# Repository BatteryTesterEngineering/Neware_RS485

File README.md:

# Neware BTS4000 RS-485 Protocol
This work is the reverse engineering of the Neware BTS4000 series battery cyclers RS-485 communication protocol.

## Division of Responsibilities
The Middle Machine is responsible for control and intepretation of the vast majority of the battery testing process, while the battery cyclers exclusively respond to commands from the middle machine.

For example, the termination conditions for test steps are evaluated and handled by the middle machine. The cyclers report current and voltage values as ADC readings, which the middle machine then converts to physical values. The testers themselves do run the active feedback control to maintain specified physical conditions: current, power, voltage, etc.

| Middle Machine   | Tester         | 
| --------- | ------------- | 
| Evaluates step termination conditions | Active feedback control to maintain step conditions (IE constant current, constant power, etc.) |
| Converts ADC values to physical values |  Sets channel LED status based on channel activity       | 
| Sets the data aquisition frequency    | Continuously Samples the ADCs  |

## RS-485 Bus
The Neware BTS4000 battery cycler system uses a full-duplex, 3 Mbps RS-485 physical bus to connect the middle machine to all of the test units.

RS-485 layout from [Neware's official guide](https://newarebattery.com/how-to-start-to-use-neware-bst4000-series/)

### Bus UART Settings

| Setting   | Value         | 
| --------- | ------------- | 
| Baud Rate | 3,000,000 bps | 
| Byte Size | 8 bits        | 
| Parity    | None          | 
| Stop Bits | 1             | 

### Full-Duplex
The RS-485 implementation by Neware is ***full-duplex***. Note that this is relatively unusual for RS-485 implementations. That means that the controller (middle machine) transmits messages on one channel (twisted copper pair), and the receivers (testers) transmit on another channel. 

> Side note: This could have been implemented as a half-duplex bus. This full-duplex communication is not technically needed, as the middle machine must send a request before any tester responds and the testers only respond after the middle machine requests. However, if the two channels are bridged, the communications fail between the middle machine and the testers. So, I guess, full-duplex it is.

### Pinout
The Neware BTS4000 middle machine and testers use RJ45 jacks and standard ethernet cables for RS-485 communications. Each machine has two ports which are wired in electrical parallel to allow for easy daisy chaining. There is no difference between the two ports.

The pinout is as follows:

| Middle Machine Function  | Tester Function | Ethernet Wire Color (T568B) | RJ45 Pin |
| ------ | ------ | ------------ | - |
| R- (B) | T- (Z) | Green        | 6 |
| R+ (A) | T+ (Y) | Green/White  | 3 |
| T- (Z) | R- (B) | Orange       | 2 |
| T+ (Y) | R+ (A) | Orange/White | 1 |
| GND    | GND    | Brown        | 8 |
| GND    | GND    | Brown/White  | 7 |

> RJ45 pins 4 and 5 (Ethernet T568B colors Blue and Blue/White) are unused.

## Neware Communication Protocol
The protocol appears to be a custom implementation on top of RS-485 and does not follow common standards such as Modbus RTU, Profibus, DMX512, BACnet MS/TP, etc.

### Overview
The middle machine begins all communications. Every response from the testers is a direct response to a request from the middle machine. The testers have a watchdog timeout such that they will turn off all charge or discharge activity on all channels if they do not hear a message from the middle machine every few seconds.

Every message is 36 bytes long and consists of one byte of machine addressing, one byte of channel addressing, one byte of message type ID, a one byte CRC, and 32 bytes of payload.

| byte 0 | byte 1 | byte 2 | byte 3 | bytes 4 - 35 |
| ------ | ------ | ------ | ------ | ------------ |
| Machine ID | Channel ID | Message Type ID | CRC | Message Type Dependent Payload

> Note: There is no time information provided by the testers. All timestamps are added upon message reception by the middle machine.

### Machine Addressing
Machine ID is 0 indexed, while it is presented to the user as 1 indexed. IE Machine ID 0 corresponds to the tester with ID 1.

### Channel Addressing
Channel ID is 0 indexed, while it is presented to the user as 1 indexed. IE Channel ID 7 corresponds to the tester Channel 8.

### Message Type ID
The message type ID byte defines what the message type is. Specifically, bit 0 is flag for request ('0' if the message is a request/comes from the middle machine) or response ('1' if the message is a response/comes from a tester), and the remaining seven bits define the message type.

| bit 0 | bits 1-7 |
| ----- | -------- |
| Request (0) / Response (1) Flag | Message Type |

Some known message type IDs are defined below:

| ID | Description |
| ----- | -------- |
| 0x00  | Tester Response (Ping) Request |
| 0x80  | Tester Presence (Ping) Acknowledge |
| 0x02  | Change Unit ID Request |
| 0x82  | Change Unit ID Acknowledge |
| 0x17  | Constant Voltage Charge Request |
| 0x97  | Constant Voltage Charge Acknowledge |
| 0x18  | Constant Voltage Discharge Request |
| 0x98  | Constant Voltage Discharge Acknowledge |
| 0x1A  | Constant Current Charge Request |
| 0x9A  | Constant Current Charge Acknowledge |
| 0x1B  | Constant Current Discharge Request |
| 0x9B  | Constant Current Discharge Acknowledge |
| 0x1C  | Constant Power Discharge Request |
| 0x9C  | Constant Power Discharge Acknowledge |
| 0x1F  | Voltage and Current Request |
| 0x9F  | Voltage and Current Acknowledge |
| 0x25  | End of Test Request |
| 0xA5  | End of Test Acknowledge |
| 0x31  | Constant Power Charge Request |
| 0xB1  | Constant Power Charge Acknowledge |

### CRC
The CRC byte is a crc8-maxim-dow calculated on a modified message. Since the CRC byte is in the middle of the message instead of at the end, the process of using it is a bit unusual. The CRC is calculated on the full 36 byte message, with a dummy 0x00 value subbed into byte 3. The calculated CRC is then swapped into byte 3 before the message is transmitted.

**Transmission CRC Calculation**:
1. Build the message as intended, leave a dummy '0x00' value in byte 3.
2. Calculate the CRC using a crc8-maxim-dow algorithm on the 36 byte message with the dummy byte.
3. Place the calculated CRC in byte 3.
4. Transmit the 36 byte message.

**Reception CRC Checking**:
1. Receive the 36 byte message.
2. Copy the CRC out of byte 3.
3. Replace byte 3 with '0x00'
4. Calculate the CRC using a crc8-maxim-dow algorithm on the 36 byte message with the dummy byte
5. Compare the calculated CRC with the stored CRC from the message, checking for equality

-- Or --

4. Append the copied CRC byte to the end of the message
5. Calculate the CRC using a crc8-maxim-dow algorithm on the now 37 byte array (message + appended CRC)
6. Check the calculated CRC for equality with '0x00'

### Payload
The payload is message type dependent. Some known payloads are described below.

**Message 0x17: Constant Voltage Charge Request**

| Name | Byte Position | Physical Value to Bus Value Mapping |
| ----- | -------- | ----- |
| Voltage  | Bytes 4-7 | Physical Value = Bus Value / 3225.6 |

**Message 0x97: Constant Voltage Charge Acknowledge**

There is no payload for a Constant Voltage Charge Acknowledge

**Message 0x1A: Constant Current Charge Request**

| Name | Byte Position | Physical Value to Bus Value Mapping |
| ----- | -------- | ----- |
| Current  | Bytes 4-7 | Physical Value = Bus Value / Current Range Divisor |
| Current Range  | Byte 8 | See Table in 0x9F: Voltage and Current Acknowledge |

**Message 0x9A: Constant Current Charge Acknowledge**

There is no payload for a Constant Current Charge Acknowledge

**Message 0x1B: Constant Current Discharge Request**

| Name | Byte Position | Physical Value to Bus Value Mapping |
| ----- | -------- | ----- |
| Current  | Bytes 4-7 | Physical Value = Bus Value / Current Range Divisor |
| Current Range  | Byte 8 | See Table in 0x9F: Voltage and Current Acknowledge |

**Message 0x9B: Constant Current Discharge Acknowledge**

There is no payload for a Constant Current Discharge Acknowledge

**Message 0x1C: Constant Power Discharge Request**

| Name | Byte Position | Physical Value to Bus Value Mapping |
| ----- | -------- | ----- |
| Power  | Bytes 4-7 | Physical Value = Bus Value / Power Range Divisor |
| Power Range  | Byte 12 | See Table |

Strangely, only power range of 0x02 has ever been seen in logs, when setting the power value from 0.5W to 60W

| Power Range | Name | Description | Power Range Divisor |
| ----- | -------- | ----- | -------- |
| 0x00  | Low Range | ? A | ? |
| 0x01  | Mid Range | ? A | ? |
| 0x02  | High Range | 0 - 60 W | 268.8 |

**Message 0x9C: Constant Power Discharge Acknowledge**

There is no payload for a Constant Power Discharge Acknowledge

**Message 0x1F: Voltage and Current Request**

There is no payload for a Voltage and Current Request

**Message 0x9F: Voltage and Current Acknowledge**

| Name | Byte Position | Physical Value to Bus Value Mapping |
| ----- | -------- | ----- |
| Voltage  | Bytes 4-7 | Physical Value = Bus Value / 3225.6 |
| Current  | Bytes 8-11 | Physical Value = Bus Value / Current Range Divisor |
| Current Range  | Byte 33 | See Table |
| Channel Status | Byte 35 | See Table |

| Current Range | Name | Description | Current Range Divisor |
| ----- | -------- | ----- | -------- |
| 0x00  | Low Range | 0 - 1 A | 16128 |
| 0x01  | Mid Range | 1 - 6 A | 2688 |
| 0x02  | High Range | 6 - 12 A | 1344 |

| Channel Status | Description |
| ----- | ----- |
| 0x00  | Channel Active |
| 0x01  | Channel Invalid/Error |
| 0x02  | Channel Rest |

**Message 0x25: End of Test Request**

There is no payload for an End of Test Request

**Message 0xA5: End of Test Acknowledge**

There is no payload for an End of Test Acknowledge

**Message 0x31: Constant Power Charge Request**

| Name | Byte Position | Physical Value to Bus Value Mapping |
| ----- | -------- | ----- |
| Power  | Bytes 4-7 | Physical Value = Bus Value / Power Range Divisor |
| Power Range  | Byte 12 | See Table |

Strangely, only power range of 0x02 has ever been seen in logs, when setting the power value from 0.5W to 60W

| Power Range | Name | Description | Power Range Divisor |
| ----- | -------- | ----- | -------- |
| 0x00  | Low Range | ? A | ? |
| 0x01  | Mid Range | ? A | ? |
| 0x02  | High Range | 0 - 60 W | 268.8 |

**Message 0xB1: Constant Power Charge Acknowledge**

There is no payload for a Constant Power Charge Acknowledge

***TODO! Add more***

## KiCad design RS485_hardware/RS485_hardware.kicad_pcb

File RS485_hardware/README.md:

# Neware BTS4000 RS485 USB Interface

This is the Kicad project and output files for a USB Adapter that allows any computer to listen and transmit on the Neware BTS4000 RS485 bus. The adapter is based on the FTDI FT232RN chip, which includes drivers for all major operating systems. The transciever is a MaxLinear SP3077E, which allows for full duplex 3MBaud communication.

## RS485 Bus Connectors
The bus connectors are intended to duplicate the RS485 bus connections on a Middle Machine or Battery Tester. There are 2 RJ45 Jacks which are wired in parallel, allowing the device to be used in the same daisy-chain fashion as a Neware device. 

## Switches
The adapter includes 2 slide switches.

### Switch 1
Toggles the adapter between "Middle Machine Mode" and "Tester Mode". Since the RS485 bus is a full duplex bus, it matters which line the adapter is receiving on, and which it is transmitting on. With the switch slid towards the RJ45 jacks, the adapter acts as a middle machine, receiving on the same line that battery testers are transmitting on, and transmitting on the line that battery testers are receiving on. With the switch slid towards the USB-C jack, the adapter acts as tester, receiving from the middle machine and transmitting to the middle machine.

| Switch Position | Adapter Mode | Adapter TX | Adapter RX | LED Color |
| ------ | ------ | ------ | ------ | ------ |
| Towards RJ45 | Middle Machine | Middle Machine TX | Middle Machine RX | Blue |
| Towards USB-C | Tester | Middle Machine RX | Middle Machine TX | Red |

### Switch 2
Toggles the RS485 Termination Resistors on or off. With the switch slid towards the RJ45 jacks, there are no termination resistors on the bus. With the switch slid towards the USB-C jack, the adapter terminates the TX and RX busses with a 120Ω resistor on each bus. Whether or not you need the termination resistors enabled dependes on the length of the bus and what other devices are on the bus. A typical RS485 bus has a temination resistor enabled on both physical ends of the bus.

## PC Connection
The connection to a computer is a USB-C connector configured to run at USB 2.0 speeds. The USB connector has 5.1kΩ resistors on the CC lines, which allow it to work with USB C<->C cables or USB A<->C cables.

# Manufacturing
The ```outputs/manufacturing_files``` subfolder contains gerber and OBD files needed for PCB manufacturing, as well as the BOM file. The BOM contains manufacturer and part number data for digikey and LCSC to make sourcing parts easy regardless of where the boards are manufactured.

## Hand Assembly
All passives are 0603 or larger, with the large-pad footprints chosen to allow for hand soldering. Similarly, the pitch of all components should be large enough for hand soldering.

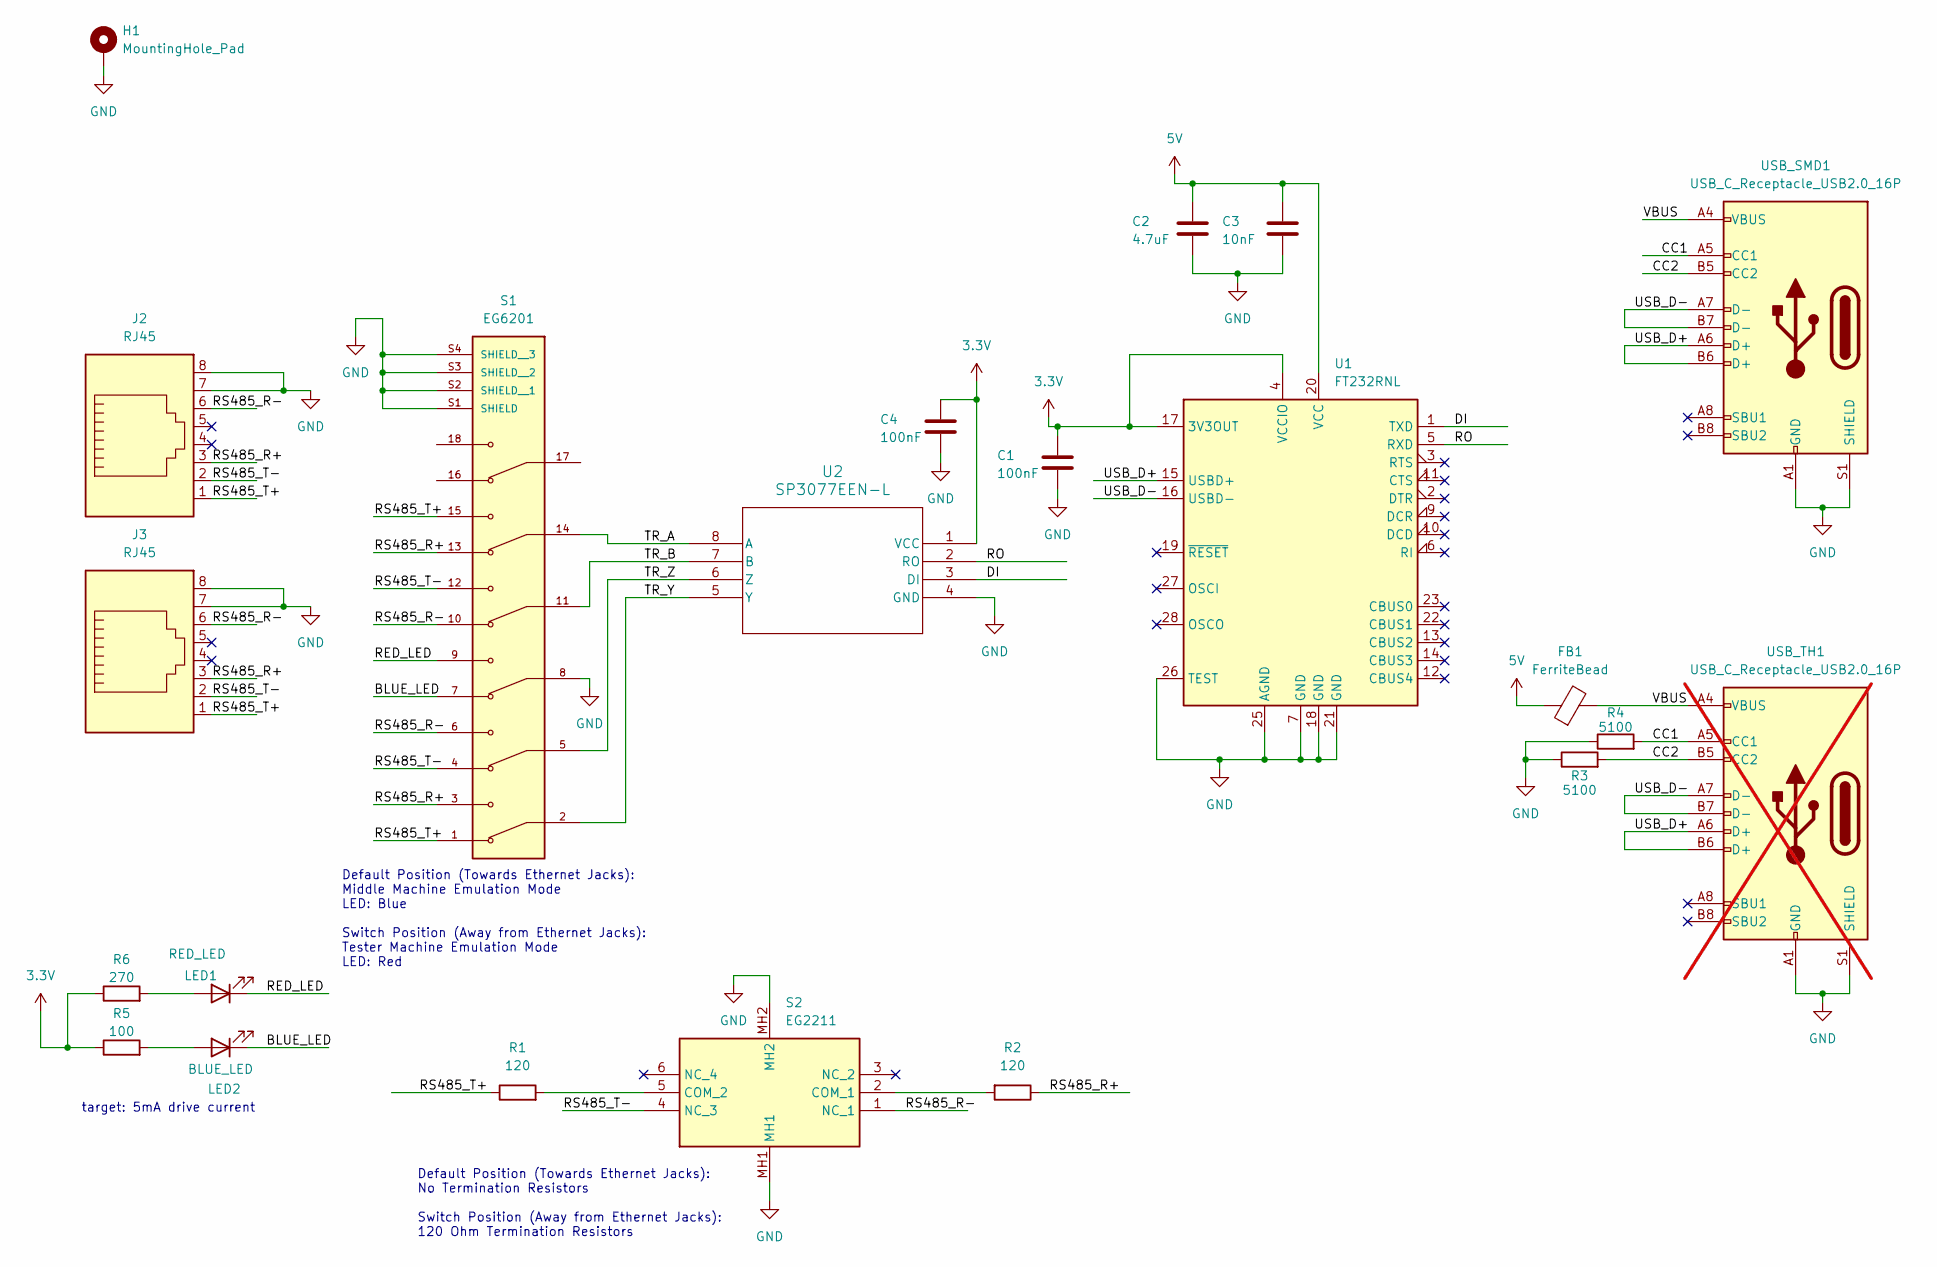
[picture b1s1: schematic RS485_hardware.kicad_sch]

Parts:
C1, C4: 100nF; C_0603_1608Metric_Pad1.08x0.95mm_HandSolder
C2: 4.7uF; C_0603_1608Metric_Pad1.08x0.95mm_HandSolder
C3: 10nF; C_0603_1608Metric_Pad1.08x0.95mm_HandSolder
FB1: FerriteBead; L_0805_2012Metric_Pad1.05x1.20mm_HandSolder
H1: MountingHole_Pad; MountingHole_3.2mm_M3_DIN965_Pad
J2, J3: RJ45; RJ45_Amphenol_54602-x08_Horizontal
LED1: RED_LED; LED_0603_1608Metric_Pad1.05x0.95mm_HandSolder
LED2: BLUE_LED; LED_0603_1608Metric_Pad1.05x0.95mm_HandSolder
R1, R2: 120; R_0603_1608Metric_Pad0.98x0.95mm_HandSolder
R3, R4: 5100; R_0603_1608Metric_Pad0.98x0.95mm_HandSolder
R5: 100; R_0603_1608Metric_Pad0.98x0.95mm_HandSolder
R6: 270; R_0603_1608Metric_Pad0.98x0.95mm_HandSolder
S1: EG6201; SW_EG6201; PARTREV B
S2: EG2211; Mouser Part Number 612-EG2211
U1: FT232RNL; SSOP-28_5.3x10.2mm_P0.65mm
U2: SP3077EEN-L; SOIC8_3P99X4P98
USB_SMD1: USB_C_Receptacle_USB2.0_16P; USB_C_Receptacle_GCT_USB4105-xx-A_16P_TopMnt_Horizontal
USB_TH1: USB_C_Receptacle_USB2.0_16P; USB_C_Receptacle_GCT_USB4085; not fitted

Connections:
3.3V: C1.1, C4.1, R5.1, R6.1, U1.4 (VCCIO), U1.17 (3V3OUT), U2.1 (VCC)
5V: C2.1, C3.1, FB1.1, U1.20 (VCC)
/BLUE_LED: LED2.1 (K), S1.7
/CC1: R4.2, USB_SMD1.A5 (CC1), USB_TH1.A5 (CC1)
/CC2: R3.2, USB_SMD1.B5 (CC2), USB_TH1.B5 (CC2)
/DI: U1.1 (TXD), U2.3 (DI)
/RED_LED: LED1.1 (K), S1.9
/RO: U1.5 (RXD), U2.2 (RO)
/RS485_R+: J2.3, J3.3, R2.1, S1.3, S1.13
/RS485_R-: J2.6, J3.6, S1.6, S1.10, S2.1 (NC_1)
/RS485_T+: J2.1, J3.1, R1.1, S1.1, S1.15
/RS485_T-: J2.2, J3.2, S1.4, S1.12, S2.4 (NC_3)
/TR_A: S1.14, U2.8 (A)
/TR_B: S1.11, U2.7 (B)
/TR_Y: S1.2, U2.5 (Y)
/TR_Z: S1.5, U2.6 (Z)
/USB_D+: U1.15 (USBD+), USB_SMD1.A6 (D+), USB_SMD1.B6 (D+), USB_TH1.A6 (D+), USB_TH1.B6 (D+)
/USB_D-: U1.16 (USBD-), USB_SMD1.A7 (D-), USB_SMD1.B7 (D-), USB_TH1.A7 (D-), USB_TH1.B7 (D-)
/VBUS: FB1.2, USB_SMD1.A4 (VBUS), USB_SMD1.A9 (VBUS), USB_SMD1.B4 (VBUS), USB_SMD1.B9 (VBUS), USB_TH1.A4 (VBUS), USB_TH1.A9 (VBUS), USB_TH1.B4 (VBUS), USB_TH1.B9 (VBUS)
GND: C1.2, C2.2, C3.2, C4.2, H1.1, J2.7, J2.8, J3.7, J3.8, R3.1, R4.1, S1.8, S1.S1 (SHIELD), S1.S2 (SHIELD__1), S1.S3 (SHIELD__2), S1.S4 (SHIELD__3), S2.MH1, S2.MH2, U1.7 (GND), U1.18 (GND), U1.21 (GND), U1.25 (AGND), U1.26 (TEST), U2.4 (GND), USB_SMD1.A1 (GND), USB_SMD1.A12 (GND), USB_SMD1.B1 (GND), USB_SMD1.B12 (GND), USB_SMD1.S1 (SHIELD), USB_TH1.A1 (GND), USB_TH1.A12 (GND), USB_TH1.B1 (GND), USB_TH1.B12 (GND), USB_TH1.S1 (SHIELD)
unnamed: LED1.2 (A), R6.2
unnamed: LED2.2 (A), R5.2
unnamed: R2.2, S2.2 (COM_1)
unnamed: R1.2, S2.5 (COM_2)

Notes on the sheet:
Default Position (Towards Ethernet Jacks): Middle Machine Emulation Mode LED: Blue Switch Position (Away from Ethernet Jacks): Tester Machine Emulation Mode LED: Red
target: 5mA drive current
Default Position (Towards Ethernet Jacks): No Termination Resistors Switch Position (Away from Ethernet Jacks): 120 Ohm Termination Resistors

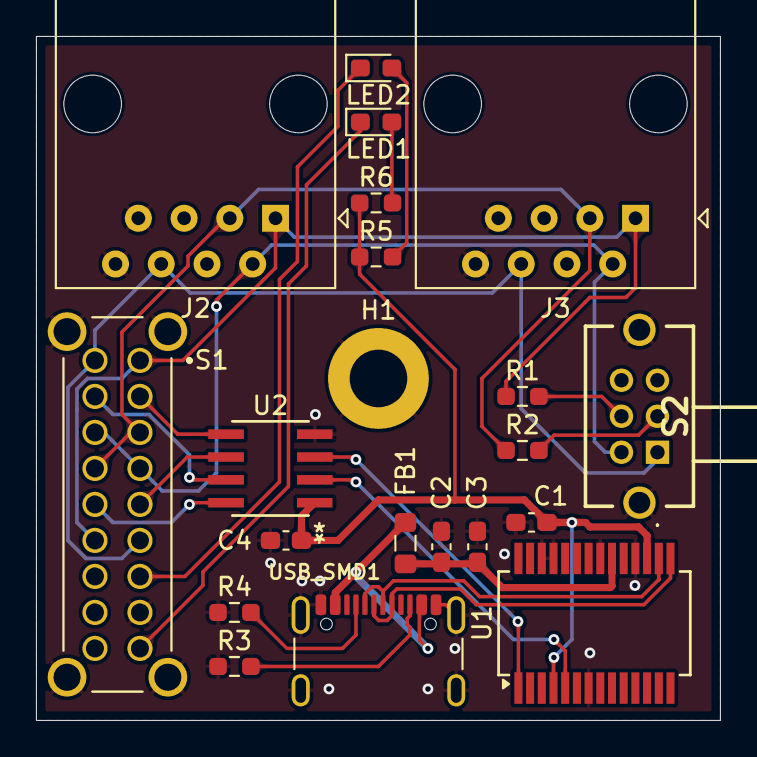
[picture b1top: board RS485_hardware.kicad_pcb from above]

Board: 2 copper layers, 38.0 x 38.0 mm, 21 parts (0 on the bottom side), 24 nets.

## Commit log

2025-05-19 initial release
